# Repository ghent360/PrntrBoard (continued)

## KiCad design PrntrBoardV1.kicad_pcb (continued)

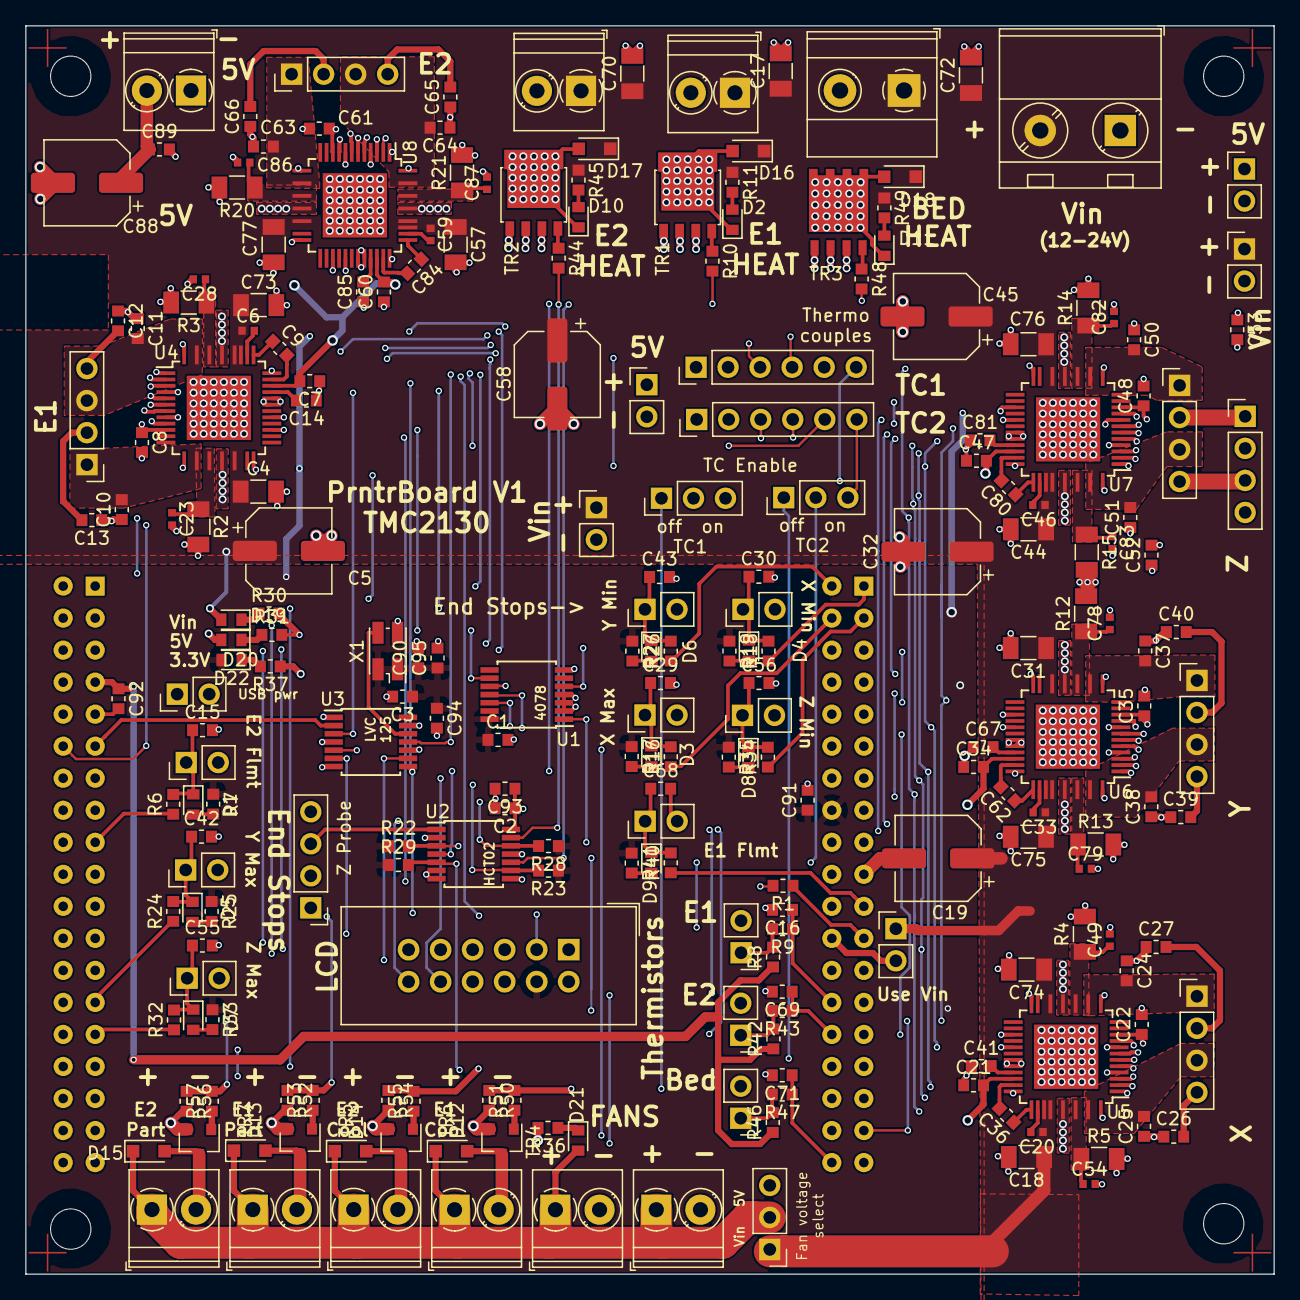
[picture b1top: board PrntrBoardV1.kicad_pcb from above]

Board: 4 copper layers, 99.0 x 99.0 mm, 238 parts (1 on the bottom side), 165 nets.

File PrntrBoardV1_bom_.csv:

Component,Description,Part,References,Value,Footprint,Quantity Per PCB,Datasheet
1,Unpolarized capacitor,C,C9 C36 C62 C80 C84,0.022uF 50V,C_0603_1608Metric,5,
2,Unpolarized capacitor,C,C1 C2 C3 C8 C14 C22 C35 C41 C48 C61 C67 C81 C85,0.1uF,C_0603_1608Metric,13,
3,Unpolarized capacitor,C,C6 C20 C23 C28 C33 C46 C49 C54 C59 C78 C79 C82 C83 C86 C87,0.1uF 50V,C_0603_1608Metric,15,
4,Unpolarized capacitor,C,C7 C21 C34 C47 C60,0.47uF,C_0603_1608Metric,5,
5,Unpolarized capacitor,C,C15 C16 C29 C30 C42 C43 C55 C56 C68 C69 C71 C89,1000pF,C_0603_1608Metric,12,
6,Unpolarized capacitor,C,C10 C11 C12 C13 C24 C25 C26 C27 C37 C38 C39 C40 C50 C51 C52 C53 C63 C64 C65 C66,1000pF >50V,C_0603_1608Metric,20,
7,Polarised capacitor,CP,C88,100uF,CP_Elec_6.3x7.7,1,
8,Polarised capacitor,CP1_Small,C5 C19 C32 C45 C58,100uF 35V,CP_Elec_6.3x7.7,5,
9,Polarised capacitor,CP1_Small,C17 C70 C72,10uF 35V,CP_Elec_4x5.3,3,
10,Unpolarized capacitor,C,C4 C18 C31 C44 C57 C73 C74 C75 C76 C77,10uF 50V,C_1206_3216Metric,10,
11,Diode,D,D12 D13 D14 D15 D16 D17 D18,1N4148,D_SOD-323F,7,
12,LED generic,LED,D2 D10 D11,HEATER,LED_0603_1608Metric,3,
13,LED generic,LED,D1 D3 D4 D5 D6 D7 D8 D9,LED,LED_0603_1608Metric,8,
14,"Generic screw terminal, single row, 01x02, script generated (kicad-library-utils/schlib/autogen/connector/)",Screw_Terminal_01x02,J29,12-24V,"TerminalBlock_Phoenix_MKDS-1,5-2-5.08_1x02_P5.08mm_Horizontal",1,
15,"Generic screw terminal, single row, 01x02, script generated (kicad-library-utils/schlib/autogen/connector/)",Screw_Terminal_01x02,J8,Always On Fan 1,"TerminalBlock_Phoenix_PT-1,5-2-3.5-H_1x02_P3.50mm_Horizontal",1,
16,"Generic screw terminal, single row, 01x02, script generated (kicad-library-utils/schlib/autogen/connector/)",Screw_Terminal_01x02,J9,Always On Fan 2,"TerminalBlock_Phoenix_PT-1,5-2-3.5-H_1x02_P3.50mm_Horizontal",1,
17,"Generic screw terminal, single row, 01x02, script generated (kicad-library-utils/schlib/autogen/connector/)",Screw_Terminal_01x02,J2,Bed Heater,"TerminalBlock_Phoenix_MKDS-1,5-2-5.08_1x02_P5.08mm_Horizontal",1,
18,"Generic screw terminal, single row, 01x02, script generated (kicad-library-utils/schlib/autogen/connector/)",Screw_Terminal_01x02,J4,E0 Cool,"TerminalBlock_Phoenix_PT-1,5-2-3.5-H_1x02_P3.50mm_Horizontal",1,
19,"Generic screw terminal, single row, 01x02, script generated (kicad-library-utils/schlib/autogen/connector/)",Screw_Terminal_01x02,J5,E0 Part,"TerminalBlock_Phoenix_PT-1,5-2-3.5-H_1x02_P3.50mm_Horizontal",1,
20,"Generic screw terminal, single row, 01x02, script generated (kicad-library-utils/schlib/autogen/connector/)",Screw_Terminal_01x02,J6,E1 Cool,"TerminalBlock_Phoenix_PT-1,5-2-3.5-H_1x02_P3.50mm_Horizontal",1,
21,"Generic screw terminal, single row, 01x02, script generated (kicad-library-utils/schlib/autogen/connector/)",Screw_Terminal_01x02,J7,E1 Part,"TerminalBlock_Phoenix_PT-1,5-2-3.5-H_1x02_P3.50mm_Horizontal",1,
22,"Generic screw terminal, single row, 01x02, script generated (kicad-library-utils/schlib/autogen/connector/)",Screw_Terminal_01x02,J1,EXT 5V,"TerminalBlock_Phoenix_PT-1,5-2-3.5-H_1x02_P3.50mm_Horizontal",1,
23,"Generic connector, single row, 01x02, script generated (kicad-library-utils/schlib/autogen/connector/)",Conn_01x02,J30,Ext Motor Clock,PinHeader_1x02_P2.54mm_Vertical,1,
24,"Generic screw terminal, single row, 01x02, script generated (kicad-library-utils/schlib/autogen/connector/)",Screw_Terminal_01x02,J11 J25,Extruder Heater,"TerminalBlock_Phoenix_PT-1,5-2-3.5-H_1x02_P3.50mm_Horizontal",2,
25,"Generic connector, double row, 02x01, this symbol is compatible with counter-clockwise, top-bottom and odd-even numbering schemes., script generated (kicad-library-utils/schlib/autogen/connector/)",Conn_02x01,J14 J16 J18,Max,PinHeader_1x02_P2.54mm_Vertical,3,
26,"Generic connector, double row, 02x01, this symbol is compatible with counter-clockwise, top-bottom and odd-even numbering schemes., script generated (kicad-library-utils/schlib/autogen/connector/)",Conn_02x01,J15 J17 J19,Min,PinHeader_1x02_P2.54mm_Vertical,3,
27,"Generic connector, double row, 02x01, this symbol is compatible with counter-clockwise, top-bottom and odd-even numbering schemes., script generated (kicad-library-utils/schlib/autogen/connector/)",Conn_02x01,J10 J24,Probe,PinHeader_1x02_P2.54mm_Vertical,2,
28,"Generic connector, single row, 01x04, script generated (kicad-library-utils/schlib/autogen/connector/)",Conn_01x04,J12 J20 J21 J22 J23 J26,Stepper,PinHeader_1x04_P2.54mm_Vertical,6,
29,"Generic connector, double row, 02x01, this symbol is compatible with counter-clockwise, top-bottom and odd-even numbering schemes., script generated (kicad-library-utils/schlib/autogen/connector/)",Conn_02x01,J13 J27 J28,Thermistor,PinHeader_1x02_P2.54mm_Vertical,3,
30,"Generic connector, single row, 01x04, script generated (kicad-library-utils/schlib/autogen/connector/)",Conn_01x04,J3,Z Probe,PinHeader_1x04_P2.54mm_Vertical,1,
31,"Jumper, 2-pole, open",Jumper_2_Open,JP3 JP4 JP5 JP6 JP7,Clock Disable,SolderJumper-2_P1.3mm_Open_Pad1.0x1.5mm,5,
32,"Jumper, 3-pole, both open",Jumper_3_Open,JP1,FAN Voltage select,PinHeader_1x03_P2.54mm_Vertical,1,
33,"Jumper, 3-pole, pins 1+2 closed/bridged",Jumper_3_Bridged12,JP2,Motor Clock Select,SolderJumper-3_P1.3mm_Open_Pad1.0x1.5mm,1,
34,Resistor,R,R2 R3 R4 R5 R12 R13 R14 R15 R20 R21,0R15 0.5W,R_1206_3216Metric,10,
35,Resistor,R,R1 R6 R9 R11 R16 R18 R24 R26 R32 R34 R40 R43 R45 R47 R49 R50 R52 R54 R56,10k,R_0603_1608Metric,19,
36,Resistor,R,R10 R44 R48,180R,R_0603_1608Metric,3,
37,Resistor,R,R7 R17 R19 R25 R27 R33 R35 R41 R51 R53 R55 R57,1k,R_0603_1608Metric,12,
38,Resistor,R,R8 R42 R46,4k7 1%,R_0603_1608Metric,3,
39,,IPD036N04L,TR3,BSC011N03LS,Texas_S-PVSON-N8_ThermalVias,1,
40,,IPD036N04L,TR1 TR2,PSMN7R0-30YL,SOT-669_LFPAK,2,
41,,BSH105,TR4 TR5 TR6 TR7,SI2318CDS,SOT-23,4,
42,,4078,U1,4078,TSSOP-14_4.4x5mm_P0.65mm,1,
43,quad 2-input NOR gate,74HCT02,U2,74HCT02,TSSOP-14_4.4x5mm_P0.65mm,1,http://www.ti.com/lit/gpn/sn74hct02
44,Quad buffer 3-State outputs,74LVC125,U3,74LVC125,TSSOP-14_4.4x5mm_P0.65mm,1,http://www.ti.com/lit/gpn/sn74LVC125
45,,NUCLEO-64,U11,NUCLEO-64,Nucleo-64,1,DOCUMENTATION
46,,TMC5130,U4 U5 U6 U7 U8,TMC5130,tmc5130-nc,5,https://www.trinamic.com/fileadmin/assets/Products/ICs_Docum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





Component Groups:,46
Component Count:,207
Fitted Components:,207
Number of PCBs:,1
Total components:,207
Schematic Version:,
Schematic Date:,
BoM Date:,Mon 23 Apr 2018 07:51:00 PM PDT
Schematic Source:,/home/vne/projects/kicad_pcbs/PrntrBoardV1/PrntrBoardV1.sch
KiCad Version:,Eeschema 5.0.0-rc2-dev-unknown-268aeeb~64~ubuntu17.10.1

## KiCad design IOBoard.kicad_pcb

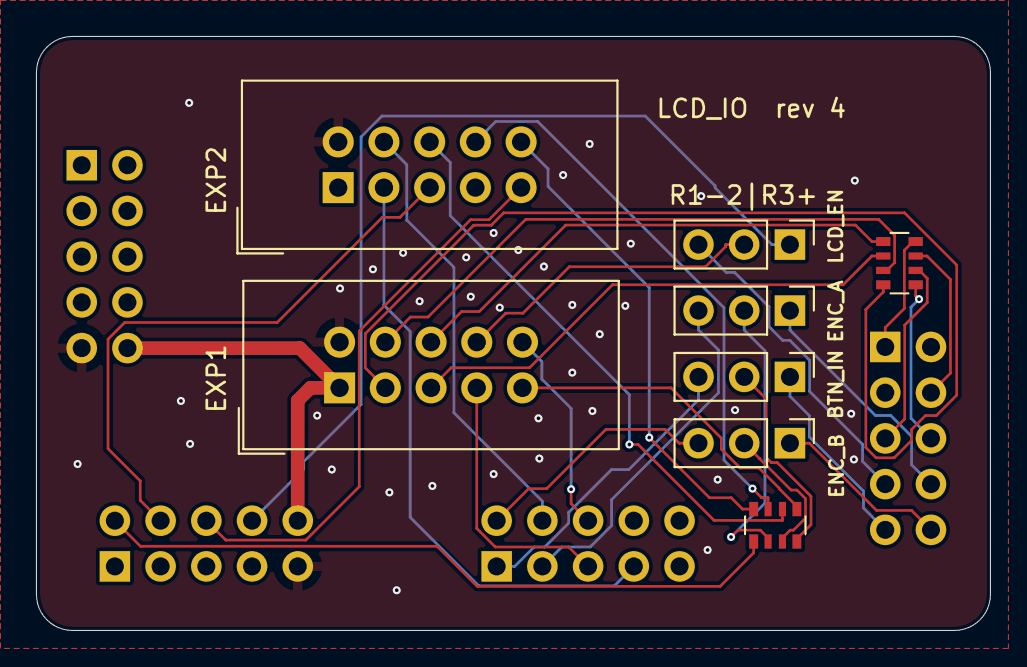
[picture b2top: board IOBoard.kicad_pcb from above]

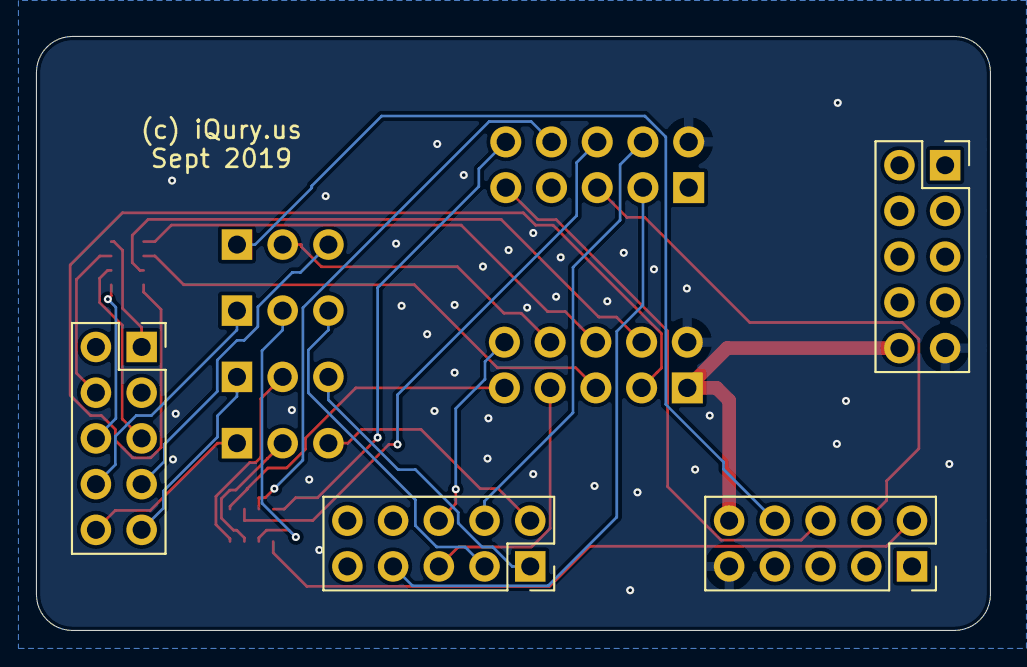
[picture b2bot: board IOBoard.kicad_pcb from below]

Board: 2 copper layers, 53.0 x 33.0 mm, 12 parts (4 on the bottom side), 33 nets.

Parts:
J1: EXP1; PinSocket_2x05_P2.54mm_Vertical
J2: EXP2; PinSocket_2x05_P2.54mm_Vertical
J3: LCD_EXP1; IDC-Header_2x05_P2.54mm_Vertical
J4: LCD_EXP2; IDC-Header_2x05_P2.54mm_Vertical
J5: EXP3; PinSocket_2x05_P2.54mm_Vertical
J6: EXP4; PinSocket_2x05_P2.54mm_Vertical
JP1: JP_BTN_IN; PinHeader_1x03_P2.54mm_Vertical
JP2: JP_ENC_B; PinHeader_1x03_P2.54mm_Vertical
JP3: JP_ENC_A; PinHeader_1x03_P2.54mm_Vertical
JP4: JP_LCD_EN; PinHeader_1x03_P2.54mm_Vertical
RN1, RN2: 4x10k; R_Array_Convex_4x0603

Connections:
/5V: J3.1, J5.10, J6.10
/BTN_ENC: J3.9, RN1.1
/BTN_IN: J2.9, JP1.1
/ENC_A: J2.8, JP3.1
/ENC_B: J2.10, JP2.1
/ENC_EN1: J4.8, RN1.3
/ENC_EN2: J4.6, RN1.2
/IOA_3: J2.1, RN2.8
/IOA_6: J2.4, RN2.7
/IOA_7: J2.5, RN2.6
/IOA_8: J2.6, RN2.5
/IOA_15: J2.7, JP4.3
/IOE_0: J1.1, JP1.3
/IOE_1: J1.2, JP2.3
/IOE_2: J1.3, JP3.3
/IOE_3: J1.4, J4.4
/IOE_4: J1.5, J3.7
/IOE_5: J1.6, J3.10
/IOE_6: J1.7, J4.3
/LCD_D4: J3.6, RN2.1
/LCD_D5: J3.5, RN2.2
/LCD_D6: J3.4, RN2.3
/LCD_D7: J3.3, RN2.4
/LCD_EN: J3.8, JP4.2
/MISO_IN: J4.10, RN1.4
/SPI2_MISO: J5.2, RN1.5
/SPI2_MOSI: J4.5, J5.4
/SPI2_SCK: J4.9, J5.6
/~LCD_CS: J5.8, JP4.1
GND: J3.2, J4.2, J5.9, J6.9
unnamed: JP1.2, RN1.8
unnamed: JP2.2, RN1.7
unnamed: JP3.2, RN1.6

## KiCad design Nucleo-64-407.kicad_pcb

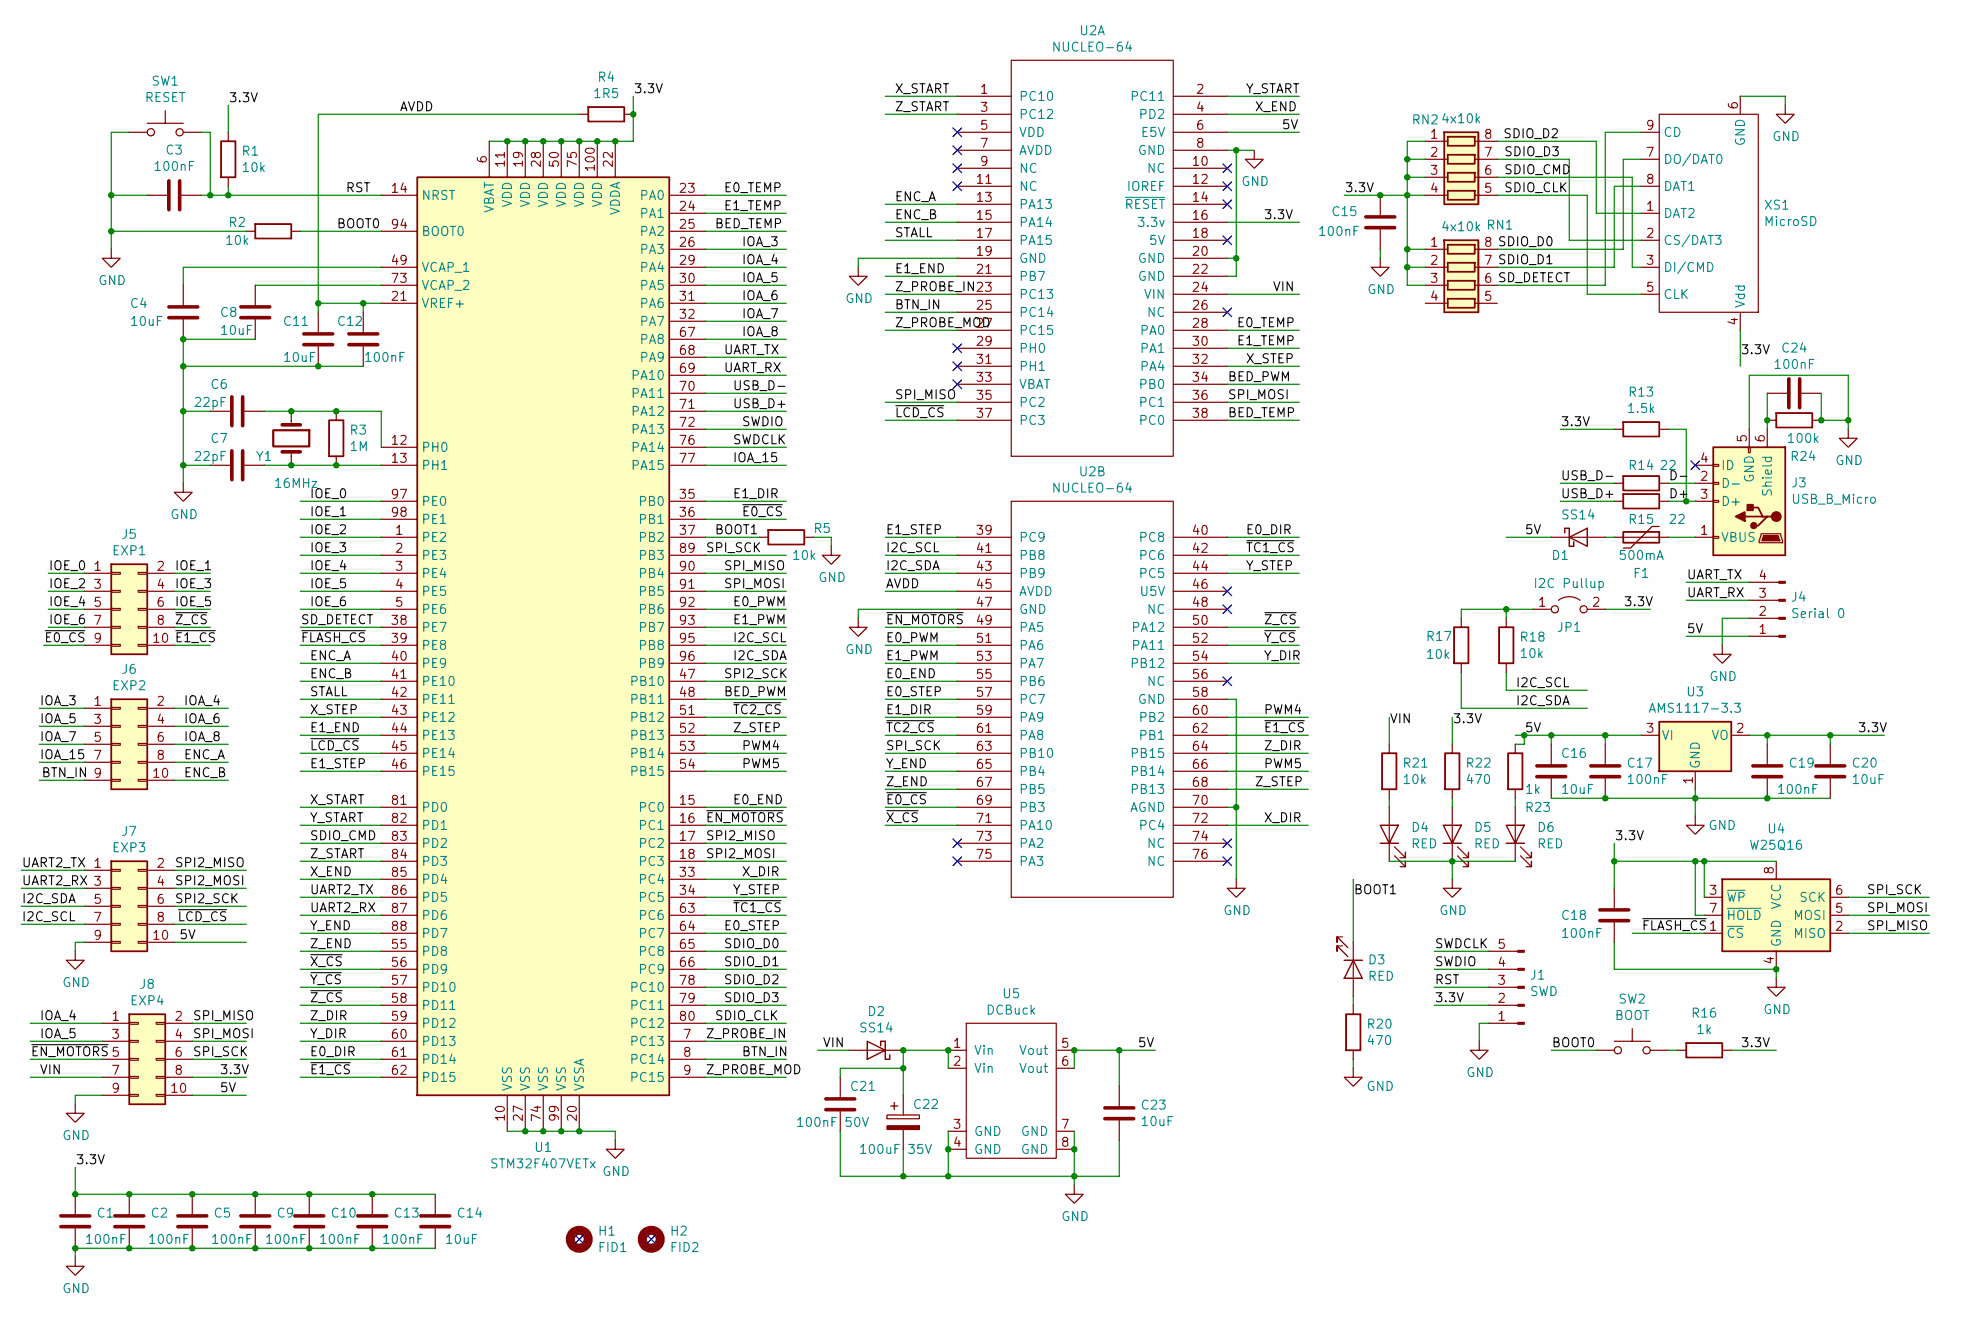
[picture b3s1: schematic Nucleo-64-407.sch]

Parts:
C1, C2, C3, C5, C9, C10, C12, C13, C15, C17, C18, C19, C24: 100nF; C_0603_1608Metric
C4, C8, C11, C14, C16, C20, C23: 10uF; C_0603_1608Metric
C6, C7: 22pF; C_0603_1608Metric
C21: 100nF 50V; C_0402_1005Metric
C22: 100uF 35V; CP_Elec_6.3x5.4
D1, D2: SS14; D_SMA
D3, D4, D5, D6: RED; D_0603_1608Metric
F1: 500mA; Fuse_0603_1608Metric
H1: FID1; Fiducial_1mm_Dia_2.54mm_Outer_CopperTop
H2: FID2; Fiducial_1mm_Dia_2.54mm_Outer_CopperTop
J1: SWD; PinHeader_1x05_P2.54mm_Vertical
J3: USB_B_Micro; MC-101C
J4: Serial 0; PinHeader_1x04_P2.54mm_Vertical
J5: EXP1; IDC-Header_2x05_P2.54mm_Vertical
J6: EXP2; IDC-Header_2x05_P2.54mm_Vertical
J7: EXP3; IDC-Header_2x05_P2.54mm_Vertical
J8: EXP4; IDC-Header_2x05_P2.54mm_Vertical
JP1: I2C Pullup; SolderJumper-2_P1.3mm_Open_TrianglePad1.0x1.5mm
R1, R2, R5, R17, R18, R21: 10k; R_0603_1608Metric
R3: 1M; R_0603_1608Metric
R4: 1R5; R_0603_1608Metric
R13: 1.5k; R_0603_1608Metric
R14, R15: 22; R_0603_1608Metric
R16, R23: 1k; R_0603_1608Metric
R20, R22: 470; R_0603_1608Metric
R24: 100k; R_0603_1608Metric
RN1, RN2: 4x10k; R_Array_Convex_4x0603
SW1: RESET; Button_4x4
SW2: BOOT; Button_4x4
U1: STM32F407VETx; LQFP-100_14x14mm_P0.5mm
U2: NUCLEO-64; Nucleo-64
U3: AMS1117-3.3; SOT-223-3_TabPin2
U4: W25Q16; SO-8_5.3x6.2mm_P1.27mm
U5: DCBuck; Buck2217
XS1: MicroSD; Conn_uSDcard
Y1: 16MHz; Crystal_SMD_HC49-SD

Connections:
/3.3V: C1.1, C2.1, C5.1, C9.1, C10.1, C13.1, C14.1, C15.1, C18.1, C19.1, C20.1, J1.2, J8.8, JP1.2 (B), R1.1, R4.1, R13.2, R16.1, R22.1, RN1.1 (R1.1), RN1.2 (R2.1), RN1.3 (R3.1), RN2.1 (R1.1), RN2.2 (R2.1), RN2.3 (R3.1), RN2.4 (R4.1), U1.6 (VBAT), U1.11 (VDD), U1.19 (VDD), U1.22 (VDDA), U1.28 (VDD), U1.50 (VDD), U1.75 (VDD), U1.100 (VDD), U2.16 (3.3v), U3.2 (VO), U4.3 (~WP), U4.7 (~HOLD), U4.8 (VCC), XS1.4 (Vdd)
/5V: C16.1, C17.1, C23.1, D1.1 (K), J4.1, J7.10, J8.10, R23.1, U2.6 (E5V), U3.3 (VI), U5.5 (Vout), U5.6 (Vout)
/AVDD: C11.1, C12.1, R4.2, U1.21 (VREF+), U2.45 (AVDD)
/BED_PWM: U1.48 (PB11), U2.34 (PB0)
/BED_TEMP: U1.25 (PA2), U2.38 (PC0)
/BOOT0: R2.1, SW2.1, U1.94 (BOOT0)
/BOOT1: D3.1 (K), R5.2, U1.37 (PB2)
/BTN_IN: J6.9, U1.8 (PC14), U2.25 (PC14)
/D+: J3.3 (D+), R13.1, R15.1
/D-: J3.2 (D-), R14.1
/E0_DIR: U1.61 (PD14), U2.40 (PC8)
/E0_END: U1.15 (PC0), U2.55 (PB6)
/E0_PWM: U1.92 (PB6), U2.51 (PA6)
/E0_STEP: U1.64 (PC7), U2.57 (PC7)
/E0_TEMP: U1.23 (PA0), U2.28 (PA0)
/E1_DIR: U1.35 (PB0), U2.59 (PA9)
/E1_END: U1.44 (PE13), U2.21 (PB7)
/E1_PWM: U1.93 (PB7), U2.53 (PA7)
/E1_STEP: U1.46 (PE15), U2.39 (PC9)
/E1_TEMP: U1.24 (PA1), U2.30 (PA1)
/ENC_A: J6.8, U1.40 (PE9), U2.13 (PA13)
/ENC_B: J6.10, U1.41 (PE10), U2.15 (PA14)
/I2C_SCL: J7.7, R18.2, U1.95 (PB8), U2.41 (PB8)
/I2C_SDA: J7.5, R17.2, U1.96 (PB9), U2.43 (PB9)
/IOA_3: J6.1, U1.26 (PA3)
/IOA_4: J6.2, J8.1, U1.29 (PA4)
/IOA_5: J6.3, J8.3, U1.30 (PA5)
/IOA_6: J6.4, U1.31 (PA6)
/IOA_7: J6.5, U1.32 (PA7)
/IOA_8: J6.6, U1.67 (PA8)
/IOA_15: J6.7, U1.77 (PA15)
/IOE_0: J5.1, U1.97 (PE0)
/IOE_1: J5.2, U1.98 (PE1)
/IOE_2: J5.3, U1.1 (PE2)
/IOE_3: J5.4, U1.2 (PE3)
/IOE_4: J5.5, U1.3 (PE4)
/IOE_5: J5.6, U1.4 (PE5)
/IOE_6: J5.7, U1.5 (PE6)
/PWM4: U1.53 (PB14), U2.60 (PB2)
/PWM5: U1.54 (PB15), U2.66 (PB14)
/RST: C3.1, J1.3, R1.2, SW1.2, U1.14 (NRST)
/SDIO_CLK: RN2.5 (R4.2), U1.80 (PC12), XS1.5 (CLK)
/SDIO_CMD: RN2.6 (R3.2), U1.83 (PD2), XS1.3 (DI/CMD)
/SDIO_D0: RN1.8 (R1.2), U1.65 (PC8), XS1.7 (DO/DAT0)
/SDIO_D1: RN1.7 (R2.2), U1.66 (PC9), XS1.8 (DAT1)
/SDIO_D2: RN2.8 (R1.2), U1.78 (PC10), XS1.1 (DAT2)
/SDIO_D3: RN2.7 (R2.2), U1.79 (PC11), XS1.2 (CS/DAT3)
/SD_DETECT: RN1.6 (R3.2), U1.38 (PE7), XS1.9 (CD)
/SPI2_MISO: J7.2, U1.17 (PC2)
/SPI2_MOSI: J7.4, U1.18 (PC3)
/SPI2_SCK: J7.6, U1.47 (PB10)
/SPI_MISO: J8.2, U1.90 (PB4), U2.35 (PC2), U4.2 (MISO)
/SPI_MOSI: J8.4, U1.91 (PB5), U2.36 (PC1), U4.5 (MOSI)
/SPI_SCK: J8.6, U1.89 (PB3), U2.63 (PB10), U4.6 (SCK)
/STALL: U1.42 (PE11), U2.17 (PA15)
/SWDCLK: J1.5, U1.76 (PA14)
/SWDIO: J1.4, U1.72 (PA13)
/UART2_RX: J7.3, U1.87 (PD6)
/UART2_TX: J7.1, U1.86 (PD5)
/UART_RX: J4.3, U1.69 (PA10)
/UART_TX: J4.4, U1.68 (PA9)
/USB_D+: R15.2, U1.71 (PA12)
/USB_D-: R14.2, U1.70 (PA11)
/VIN: D2.2 (A), J8.7, R21.1, U2.24 (VIN)
/X_DIR: U1.33 (PC4), U2.72 (PC4)
/X_END: U1.85 (PD4), U2.4 (PD2)
/X_START: U1.81 (PD0), U2.1 (PC10)
/X_STEP: U1.43 (PE12), U2.32 (PA4)
/Y_DIR: U1.60 (PD13), U2.54 (PB12)
/Y_END: U1.88 (PD7), U2.65 (PB4)
/Y_START: U1.82 (PD1), U2.2 (PC11)
/Y_STEP: U1.34 (PC5), U2.44 (PC5)
/Z_DIR: U1.59 (PD12), U2.64 (PB15)
/Z_END: U1.55 (PD8), U2.67 (PB5)
/Z_PROBE_IN: U1.7 (PC13), U2.23 (PC13)
/Z_PROBE_MOD: U1.9 (PC15), U2.27 (PC15)
/Z_START: U1.84 (PD3), U2.3 (PC12)
/Z_STEP: U1.52 (PB13), U2.68 (PB13)
/~E0_CS: J5.9, U1.36 (PB1), U2.69 (PB3)
/~E1_CS: J5.10, U1.62 (PD15), U2.62 (PB1)
/~EN_MOTORS: J8.5, U1.16 (PC1), U2.49 (PA5)
/~FLASH_CS: U1.39 (PE8), U4.1 (~CS)
/~LCD_CS: J7.8, U1.45 (PE14), U2.37 (PC3)
/~TC1_CS: U1.63 (PC6), U2.42 (PC6)
/~TC2_CS: U1.51 (PB12), U2.61 (PA8)
/~X_CS: U1.56 (PD9), U2.71 (PA10)
/~Y_CS: U1.57 (PD10), U2.52 (PA11)
/~Z_CS: J5.8, U1.58 (PD11), U2.50 (PA12)
GND: C1.2, C2.2, C3.2, C4.1, C5.2, C6.2, C7.2, C8.1, C9.2, C10.2, C11.2, C12.2, C13.2, C14.2, C15.2, C16.2, C17.2, C18.2, C19.2, C20.2, C21.2, C22.2, C23.2, C24.1, D4.1 (K), D5.1 (K), D6.1 (K), J1.1, J3.5 (GND), J4.2, J7.9, J8.9, R2.2, R5.1, R20.2, R24.1, SW1.1, U1.10 (VSS), U1.20 (VSSA), U1.27 (VSS), U1.74 (VSS), U1.99 (VSS), U2.8 (GND), U2.19 (GND), U2.20 (GND), U2.22 (GND), U2.47 (GND), U2.58 (GND), U2.70 (AGND), U3.1 (GND), U4.4 (GND), U5.3 (GND), U5.4 (GND), U5.7 (GND), U5.8 (GND), XS1.6 (GND)
unnamed: C4.2, U1.49 (VCAP_1)
unnamed: C6.1, R3.1, U1.12 (PH0), Y1.1
unnamed: C7.1, R3.2, U1.13 (PH1), Y1.2
unnamed: C8.2, U1.73 (VCAP_2)
unnamed: C21.1, C22.1, D2.1 (K), U5.1 (Vin), U5.2 (Vin)
unnamed: C24.2, J3.6 (Shield), R24.2
unnamed: D1.2 (A), F1.2
unnamed: D3.2 (A), R20.1
unnamed: D4.2 (A), R21.2
unnamed: D5.2 (A), R22.2
unnamed: D6.2 (A), R23.2
unnamed: F1.1, J3.1 (VBUS)
unnamed: JP1.1 (A), R17.1, R18.1
unnamed: R16.2, SW2.2

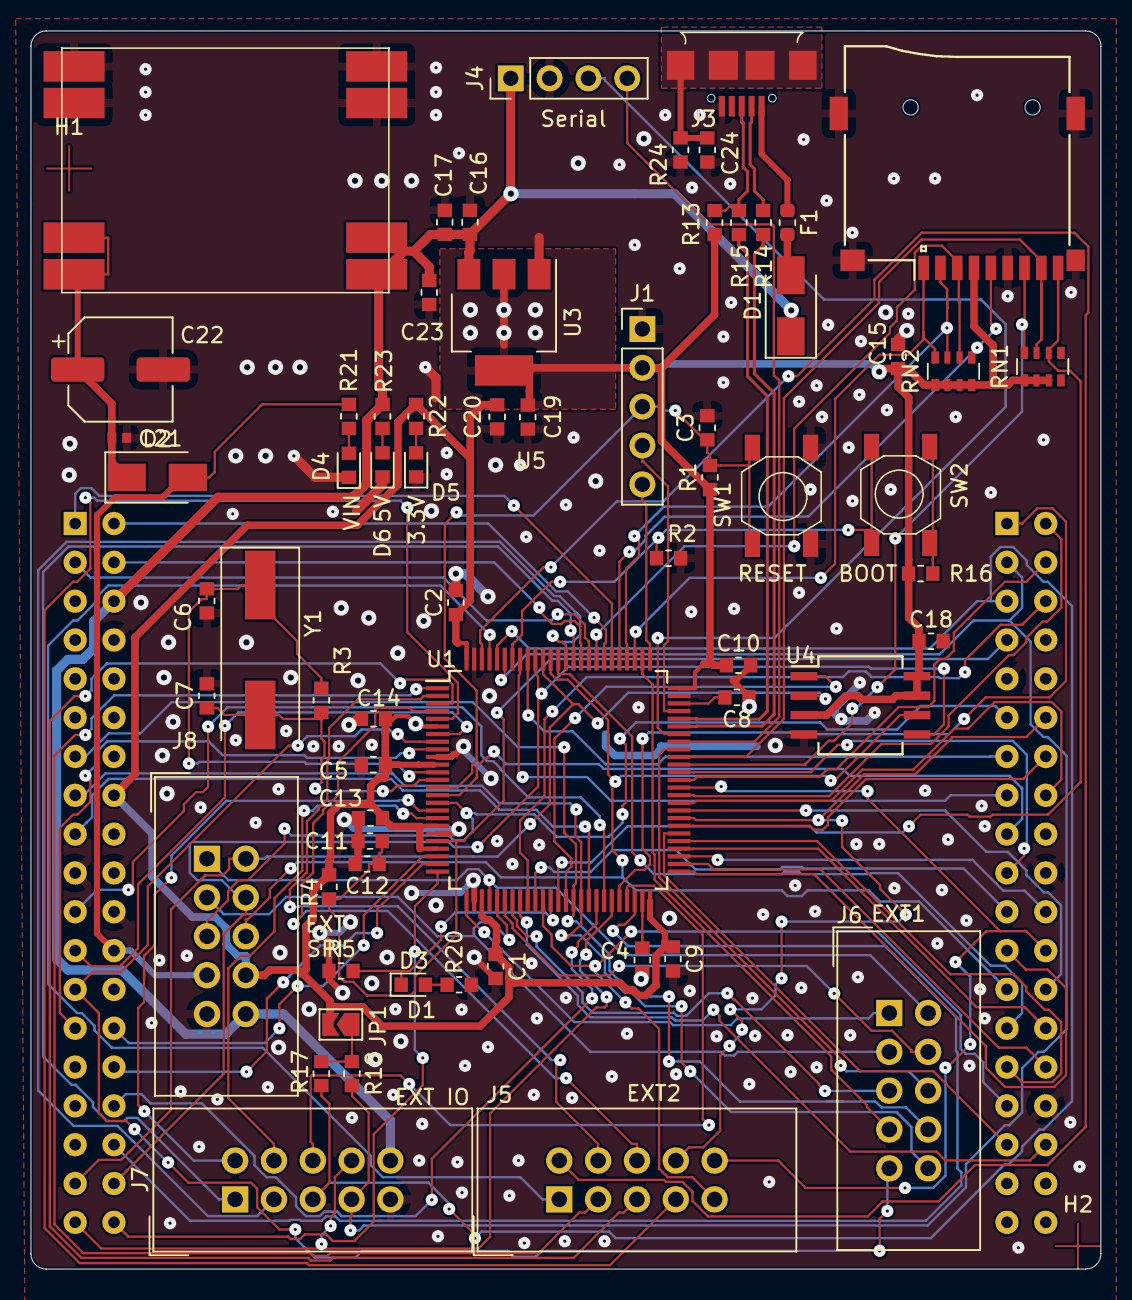
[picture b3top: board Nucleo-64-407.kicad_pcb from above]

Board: 2 copper layers, 70.0 x 81.0 mm, 68 parts (0 on the bottom side), 103 nets.

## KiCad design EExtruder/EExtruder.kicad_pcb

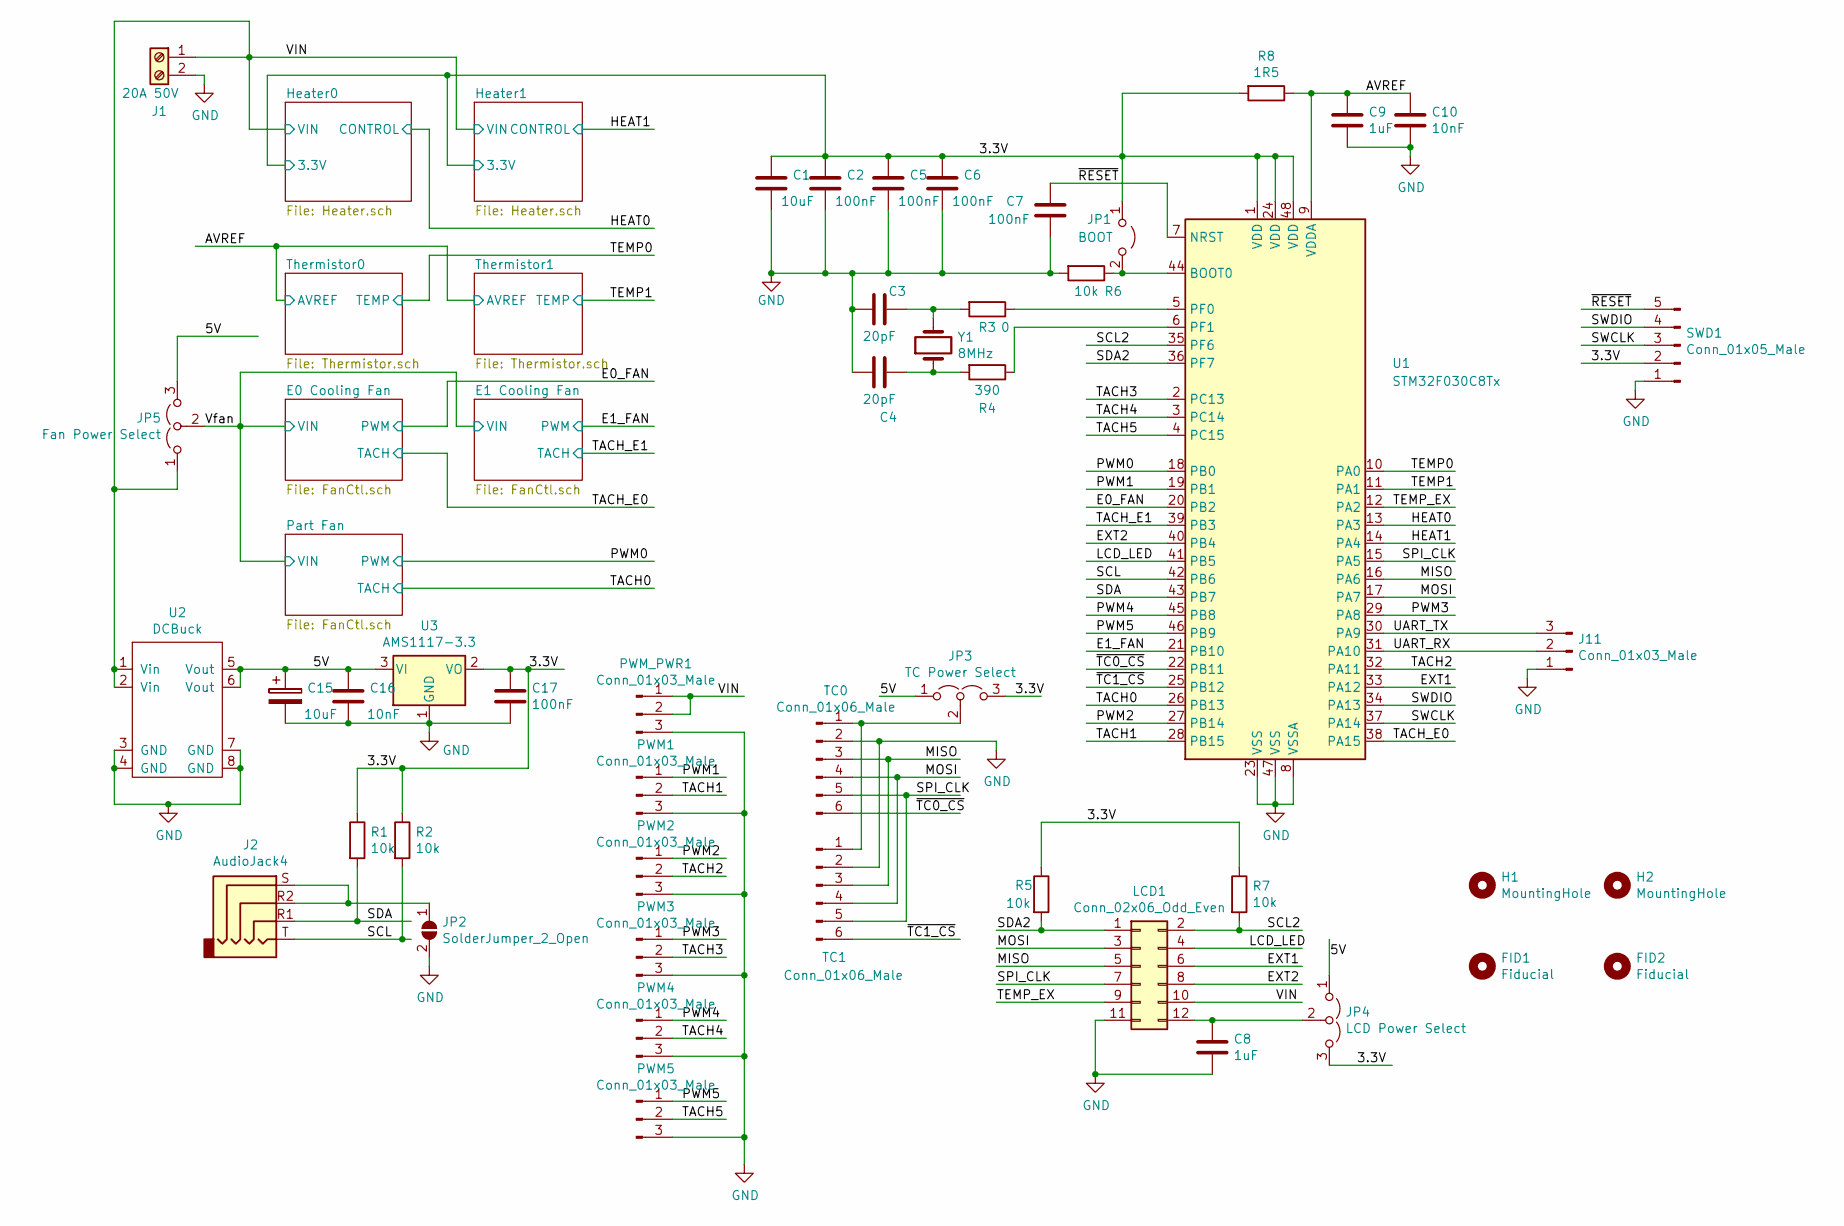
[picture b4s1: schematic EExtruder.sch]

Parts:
C1, C15: 10uF; C_0603_1608Metric
C2, C5, C6, C7, C17: 100nF; C_0603_1608Metric
C3, C4: 20pF; C_0603_1608Metric
C8, C9: 1uF; C_0603_1608Metric
C10, C16: 10nF; C_0603_1608Metric
FID1, FID2: Fiducial; Fiducial_1mm_Dia_2.54mm_Outer_CopperTop
H1, H2: MountingHole; MountingHole_3.2mm_M3
J1: 20A 50V; TerminalBlock_Phoenix_PT-1,5-2-3.5-H_1x02_P3.50mm_Horizontal
J2: AudioJack4; Jack_3.5mm_PJ320D_Horizontal
J11: Conn_01x03_Male; PinHeader_1x03_P2.54mm_Vertical
JP1: BOOT; PinHeader_1x02_P2.54mm_Vertical
JP2: SolderJumper_2_Open; SolderJumper-2_P1.3mm_Open_TrianglePad1.0x1.5mm
JP3: TC Power Select; SolderJumper-3_P1.3mm_Open_Pad1.0x1.5mm
JP4: LCD Power Select; SolderJumper-3_P1.3mm_Open_Pad1.0x1.5mm
JP5: Fan Power Select; PinHeader_1x03_P2.54mm_Vertical
LCD1: Conn_02x06_Odd_Even; IDC-Header_2x06_P2.54mm_Vertical
PWM1, PWM2, PWM3, PWM4, PWM5: Conn_01x03_Male; PinHeader_1x03_P2.54mm_Vertical
PWM_PWR1: Conn_01x03_Male; PinHeader_1x03_P2.54mm_Vertical
R1, R2, R5, R6, R7: 10k; R_0603_1608Metric
R3: 0; R_0603_1608Metric
R4: 390; R_0603_1608Metric
R8: 1R5; R_0603_1608Metric
SWD1: Conn_01x05_Male; PinHeader_1x05_P2.54mm_Vertical
TC0, TC1: Conn_01x06_Male; PinHeader_1x06_P2.54mm_Vertical
U1: STM32F030C8Tx; LQFP-48_7x7mm_P0.5mm
U2: DCBuck; Buck2217
U3: AMS1117-3.3; SOT-223-3_TabPin2
Y1: 8MHz; Crystal_SMD_HC49-SD

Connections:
/3.3V: C1.1, C2.1, C5.1, C6.1, C17.1, JP1.1 (A), JP3.3 (B), JP4.3 (B), R1.1, R2.1, R5.1, R7.1, R8.2, SWD1.2, U1.1 (VDD), U1.24 (VDD), U1.48 (VDD), U3.2 (VO); also elsewhere on the board
/5V: C15.1, C16.1, JP3.1 (A), JP4.1 (A), JP5.3 (B), U2.5 (Vout), U2.6 (Vout), U3.3 (VI)
/AVREF: C9.1, C10.1, R8.1, U1.9 (VDDA); also elsewhere on the board
/E0_FAN: U1.20 (PB2); also elsewhere on the board
/E1_FAN: U1.21 (PB10); also elsewhere on the board
/EXT1: LCD1.6, U1.33 (PA12)
/EXT2: LCD1.8, U1.40 (PB4)
/HEAT0: U1.13 (PA3); also elsewhere on the board
/HEAT1: U1.14 (PA4); also elsewhere on the board
/LCD_LED: LCD1.4, U1.41 (PB5)
/MISO: LCD1.5, TC0.3, TC1.3, U1.16 (PA6)
/MOSI: LCD1.3, TC0.4, TC1.4, U1.17 (PA7)
/PWM0: U1.18 (PB0); also elsewhere on the board
/PWM1: PWM1.1, U1.19 (PB1)
/PWM2: PWM2.1, U1.27 (PB14)
/PWM3: PWM3.1, U1.29 (PA8)
/PWM4: PWM4.1, U1.45 (PB8)
/PWM5: PWM5.1, U1.46 (PB9)
/SCL: J2.T, R2.2, U1.42 (PB6)
/SCL2: LCD1.2, R7.2, U1.35 (PF6)
/SDA: J2.R1, R1.2, U1.43 (PB7)
/SDA2: LCD1.1, R5.2, U1.36 (PF7)
/SPI_CLK: LCD1.7, TC0.5, TC1.5, U1.15 (PA5)
/SWCLK: SWD1.3, U1.37 (PA14)
/SWDIO: SWD1.4, U1.34 (PA13)
/TACH0: U1.26 (PB13); also elsewhere on the board
/TACH1: PWM1.2, U1.28 (PB15)
/TACH2: PWM2.2, U1.32 (PA11)
/TACH3: PWM3.2, U1.2 (PC13)
/TACH4: PWM4.2, U1.3 (PC14)
/TACH5: PWM5.2, U1.4 (PC15)
/TACH_E0: U1.38 (PA15); also elsewhere on the board
/TACH_E1: U1.39 (PB3); also elsewhere on the board
/TEMP0: U1.10 (PA0); also elsewhere on the board
/TEMP1: U1.11 (PA1); also elsewhere on the board
/TEMP_EX: LCD1.9, U1.12 (PA2)
/UART_RX: J11.2, U1.31 (PA10)
/UART_TX: J11.3, U1.30 (PA9)
/VIN: J1.1, JP5.1 (A), LCD1.10, PWM_PWR1.1, PWM_PWR1.2, U2.1 (Vin), U2.2 (Vin); also elsewhere on the board
/~RESET: C7.1, SWD1.5, U1.7 (NRST)
/~TC0_CS: TC0.6, U1.22 (PB11)
/~TC1_CS: TC1.6, U1.25 (PB12)
GND: C1.2, C2.2, C3.2, C4.2, C5.2, C6.2, C7.2, C8.2, C9.2, C10.2, C15.2, C16.2, C17.2, J1.2, J11.1, JP2.2 (B), LCD1.11, PWM1.3, PWM2.3, PWM3.3, PWM4.3, PWM5.3, PWM_PWR1.3, R6.2, SWD1.1, TC0.2, TC1.2, U1.8 (VSSA), U1.23 (VSS), U1.47 (VSS), U2.3 (GND), U2.4 (GND), U2.7 (GND), U2.8 (GND), U3.1 (GND); also elsewhere on the board
unnamed: C3.1, R3.2, Y1.2
unnamed: C4.1, R4.2, Y1.1
unnamed: C8.1, JP4.2 (C), LCD1.12
unnamed: J2.R2, J2.S, JP2.1 (A)
unnamed: JP1.2 (B), R6.1, U1.44 (BOOT0)
unnamed: JP3.2 (C), TC0.1, TC1.1
unnamed: R3.1, U1.5 (PF0)
unnamed: R4.1, U1.6 (PF1)

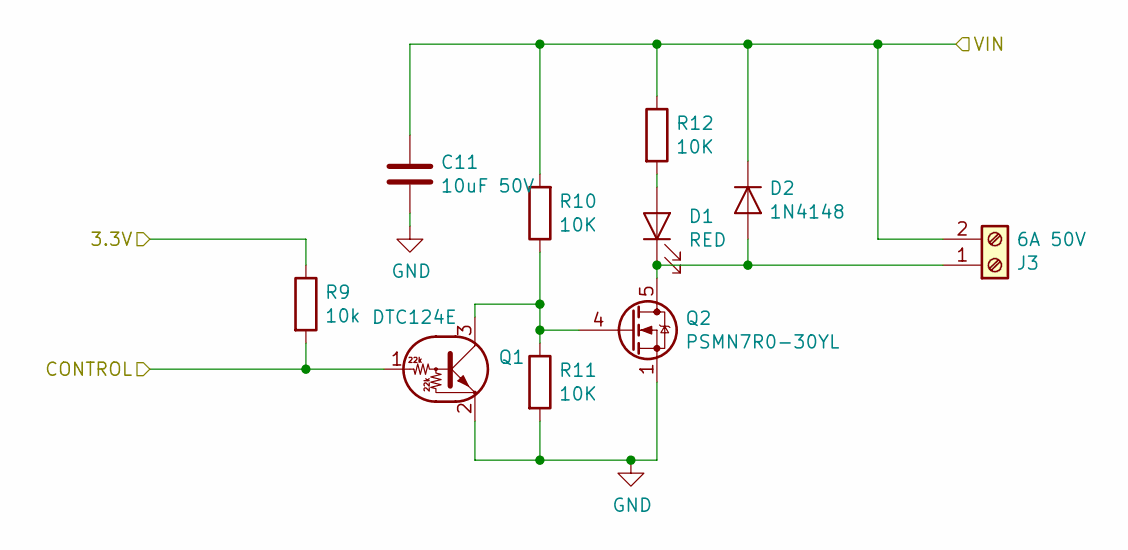
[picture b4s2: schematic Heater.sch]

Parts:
C11: 10uF 50V; C_1206_3216Metric
D1: RED; D_0603_1608Metric
D2: 1N4148; D_SOD-323_HandSoldering
J3: 6A 50V; TerminalBlock_Phoenix_PT-1,5-2-3.5-H_1x02_P3.50mm_Horizontal
Q1: DTC124E; SOT-23
Q2: PSMN7R0-30YL; LFPAK56
R9: 10k; R_0603_1608Metric
R10, R11, R12: 10K; R_0603_1608Metric

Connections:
/3.3V: R9.1; also elsewhere on the board
/HEAT0: Q1.1 (B), R9.2; also elsewhere on the board
/VIN: C11.1, D2.1 (K), J3.2, R10.2, R12.1; also elsewhere on the board
GND: C11.2, Q1.2 (E), Q2.1 (S), Q2.2 (S), Q2.3 (S), R11.2; also elsewhere on the board
unnamed: D1.1 (K), D2.2 (A), J3.1, Q2.5 (D)
unnamed: D1.2 (A), R12.2
unnamed: Q1.3 (C), Q2.4 (G), R10.1, R11.1

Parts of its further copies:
C12: 10uF 50V; C_1206_3216Metric
D3: RED; D_0603_1608Metric
D4: 1N4148; D_SOD-323_HandSoldering
J4: 6A 50V; TerminalBlock_Phoenix_PT-1,5-2-3.5-H_1x02_P3.50mm_Horizontal
Q3: DTC124E; SOT-23
Q4: PSMN7R0-30YL; LFPAK56
R13: 10k; R_0603_1608Metric
R14, R15, R16: 10K; R_0603_1608Metric

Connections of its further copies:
/3.3V: R13.1; also elsewhere on the board
/HEAT1: Q3.1 (B), R13.2; also elsewhere on the board
/VIN: C12.1, D4.1 (K), J4.2, R14.2, R16.1; also elsewhere on the board
GND: C12.2, Q3.2 (E), Q4.1 (S), Q4.2 (S), Q4.3 (S), R15.2; also elsewhere on the board
unnamed: D3.1 (K), D4.2 (A), J4.1, Q4.5 (D)
unnamed: D3.2 (A), R16.2
unnamed: Q3.3 (C), Q4.4 (G), R14.1, R15.1

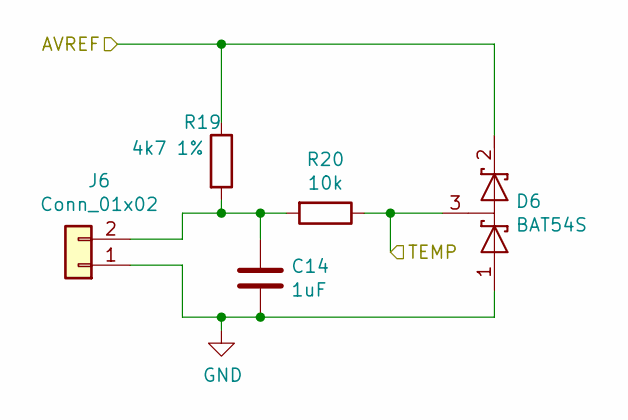
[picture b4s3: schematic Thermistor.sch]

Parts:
C13: 1uF; C_0603_1608Metric
D5: BAT54S; SOT-23
J5: Conn_01x02; PinHeader_1x02_P2.54mm_Vertical
R17: 4k7 1%; R_0603_1608Metric
R18: 10k; R_0603_1608Metric

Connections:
/AVREF: D5.2 (K), R17.1; also elsewhere on the board
/TEMP0: D5.3 (common), R18.1; also elsewhere on the board
GND: C13.2, D5.1 (A), J5.1; also elsewhere on the board
unnamed: C13.1, J5.2, R17.2, R18.2

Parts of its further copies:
C14: 1uF; C_0603_1608Metric
D6: BAT54S; SOT-23
J6: Conn_01x02; PinHeader_1x02_P2.54mm_Vertical
R19: 4k7 1%; R_0603_1608Metric
R20: 10k; R_0603_1608Metric

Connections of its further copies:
/AVREF: D6.2 (K), R19.1; also elsewhere on the board
/TEMP1: D6.3 (common), R20.1; also elsewhere on the board
GND: C14.2, D6.1 (A), J6.1; also elsewhere on the board
unnamed: C14.1, J6.2, R19.2, R20.2
